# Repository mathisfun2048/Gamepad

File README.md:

# Gamepad

## Description and Exigence
Hallo! This is my second attempt at hardware design! This time, instead of focusing on a PCB, I wanted to investigate how multiple different parts can come together to create a product. The goal of this project is to create a functional gameboy-esq device that I can play games on! Initially this project was meant to fit inside of an altoids tin, but that was above my skill grade, so I downgraded to a slighly clunkier console. 

I have always enjoyed playing video games but never really considered how the hardware was created. So, this project hit 2 birds with 1 stone: I get a super cool gaming console to add to my collection and I get to learn about hardware >:) 
This project helped me get a glimse and greater appreciation of how hard hardware desgining and moreso planning. However, I picked up some cool skills which was really fun. 

A goal I had for this project specficially was to learn how to CAD using code, which I was able to do using a python script! I can't wait to see how it looks printed out irl. I have always been into coding and its been great seeing a way to directly merge my interest for talking with computers with creating something physical. 

Okay enough yap. If you want more stream of consciousness, look at my journal ;)

## PICTURES

### Schematic

### PCB 

### project as a whole

## Firmware
So tldr I don't know how to code games (yet!) so I will be utalizing RetroPi. It is not included in this repo because 1) github was being finicky about pushing it from my desktop folder and 2) its avalible online readilly 

## BOM

Here's everything you need if you want to build this too! (also includes sweat and tears... forgot to include that in the table)

Also, you might be wonderign why everything is either from Microcenter or Adafruit and not cheaper alternatives like AliExpress. The short answer is my parents won't allow me to purchase stuff from aliexpress. However, if my cost goes above the alloted $150 with future edits or anything, I will be more than happy to pay out of pocket. If this project gets downgraded to 4 points, I'd also be willing to pay out of pocket because this is honestly pretty cool and I want to see it in person. I never got a handheld video game console as a kid and I'm excited that I'll be able to make one now :)

| Item                      | Quantity | Cost          | Source      | Link                                                                                                                                          |
| ------------------------- | -------- | ------------- | ----------- | --------------------------------------------------------------------------------------------------------------------------------------------- |
| Raspberry Pi Zero 2       | 1        | 14.99         | Microcenter | [Link](https://www.microcenter.com/product/643085/raspberry-pi-zero-2-w)                                                                      |
| GPIO header               | 1        | 5.99          | Microcenter | [Link](https://www.microcenter.com/product/480889/schmartboard-inc-schmartboard-inc-2-x-20-male-headers-qty-5)                                |
| 2.2" Display              | 1        | 24.95         | Adafruit    | [Link](https://www.adafruit.com/product/2315)                                                                                                 |
| Custom PCB                | 1        | $9 + shipping | JCL PCB     |                                                                                                                                               |
| PowerBoost 1000c          | 1        | 19.99         | Microcenter | [Link](https://www.microcenter.com/product/474415/adafruit-industries-powerboost-1000-charger-rechargeable-5v-lipo-usb-boost-@-1a)            |
| 2500 mAh Battery          | 1        | 14.99         | Adafruit | [Link](https://www.microcenter.com/product/454401/adafruit-industries-lithium-ion-polymer-battery-37v-2500mah)                                |
| stacking header           | 1        | 2.95          | Adafruit    | [Link](https://www.adafruit.com/product/1979?srsltid=AfmBOoqbo1ndLmYMVLTt_bqD4Yhi48SgEFRf9jc0nGi86ePSABa_MOBi)                                |
| Slide Switch              | 1        | 0.95          | Adafruit    | [Link](https://www.adafruit.com/product/805)                                                                                                  |
| 6mm Tactile Buttons       | 10       | 9.99          | Microcenter | [Link](https://www.microcenter.com/product/632688/inland-6x6mm-micro-momentary-tactile-push-button-switches-assortment-kit-10-values-180-pcs) |
| #4-40 3/8" Machine Screws | 14       | 0.00          | Myself      | n/a                                                                                                                                           |
| #2-56 3/8" Machine Screws | 6        | 0.00          | Myself      | n/a                                                                                                                                           |
| **Total**                 |  | **~110**      |             |

## Closing Remarks On Planning

This has been such a fun thing to fall into this rabbithole where I could desing this. Without Highway (shoutout Hack Club!) I would never have learned this much about hardware in such a short time; I am very grateful for this opportunity. While I do have to part now, I can't wait to build it and enter in my final remarks after I get this to work!

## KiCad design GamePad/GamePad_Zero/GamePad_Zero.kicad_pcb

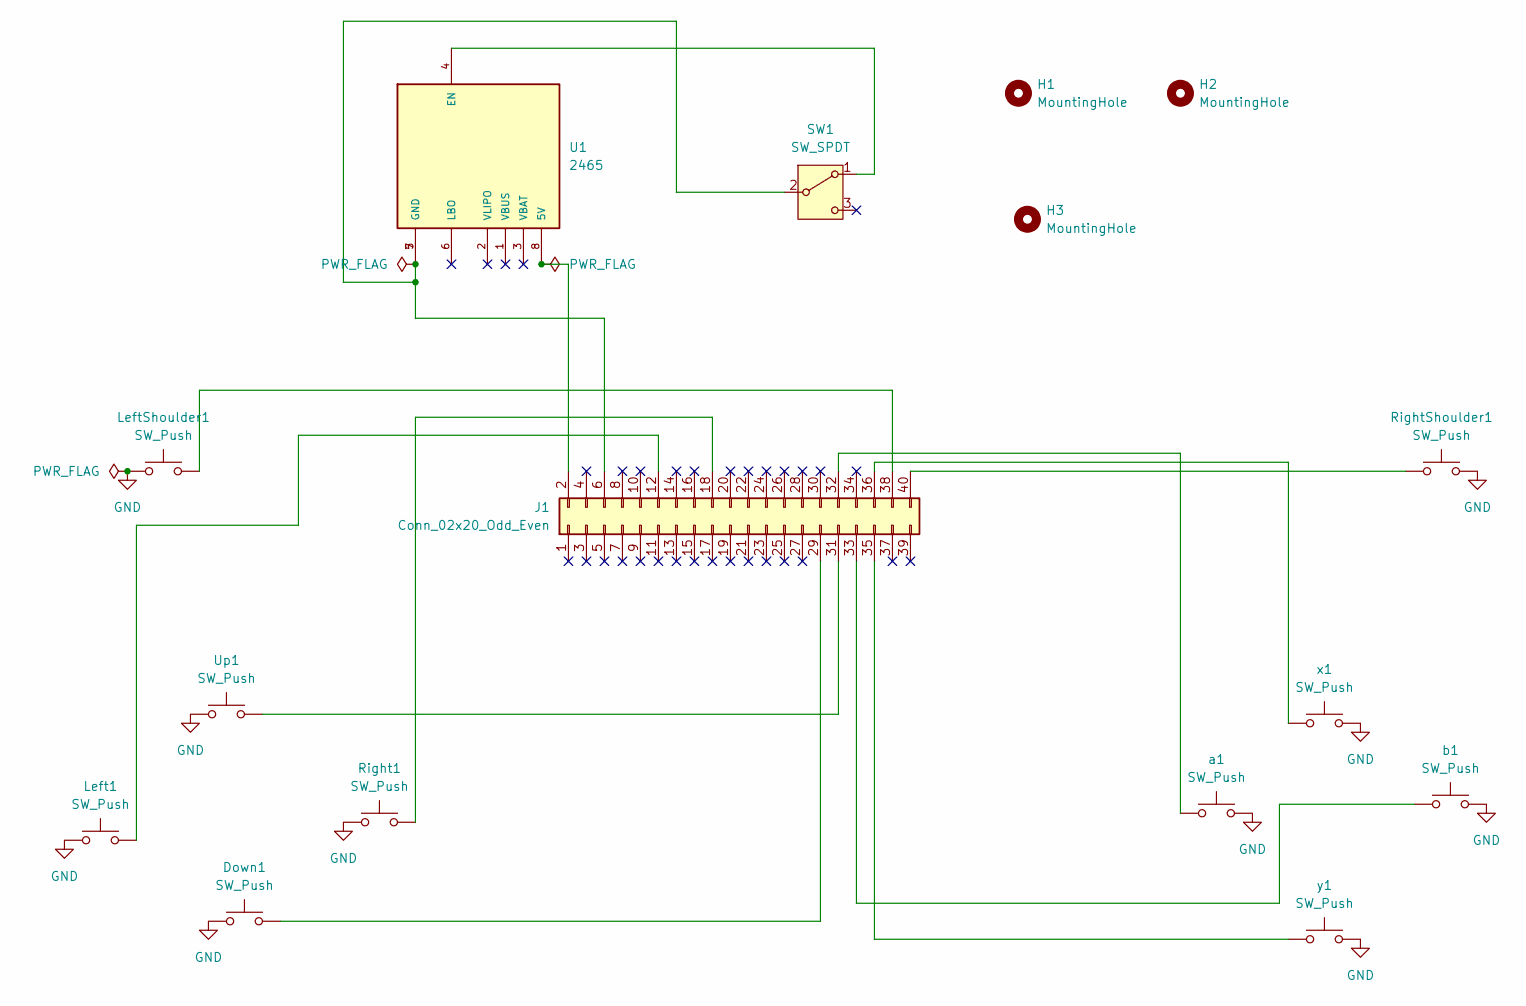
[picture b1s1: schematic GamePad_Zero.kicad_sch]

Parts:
Down1: SW_Push; SW_PUSH_6mm
H1, H2, H3: MountingHole; MountingHole_2.5mm
J1: Conn_02x20_Odd_Even; MODULE_SC1176
Left1: SW_Push; SW_PUSH_6mm
LeftShoulder1: SW_Push; SW_PUSH_6mm
Right1: SW_Push; SW_PUSH_6mm
RightShoulder1: SW_Push; SW_PUSH_6mm
SW1: SW_SPDT; SW_MINI-SPDT-SW
U1: 2465; MODULE_2465; PARTREV B
Up1: SW_Push; SW_PUSH_6mm
a1: SW_Push; SW_PUSH_6mm
b1: SW_Push; SW_PUSH_6mm
x1: SW_Push; SW_PUSH_6mm
y1: SW_Push; SW_PUSH_6mm

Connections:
GND: Down1.1, Left1.1, LeftShoulder1.1, Right1.1, RightShoulder1.2, Up1.1, a1.2, b1.2, x1.2, y1.2
unnamed: J1.2, U1.8 (5V)
unnamed: J1.6, SW1.2 (B), U1.5 (GND), U1.7 (GND)
unnamed: J1.12, Left1.2
unnamed: J1.18, Right1.2
unnamed: Down1.2, J1.29
unnamed: J1.31, Up1.2
unnamed: J1.32, a1.1
unnamed: J1.33, b1.1
unnamed: J1.35, y1.1
unnamed: J1.36, x1.1
unnamed: J1.38, LeftShoulder1.2
unnamed: J1.40, RightShoulder1.1
unnamed: SW1.1 (A), U1.4 (EN)

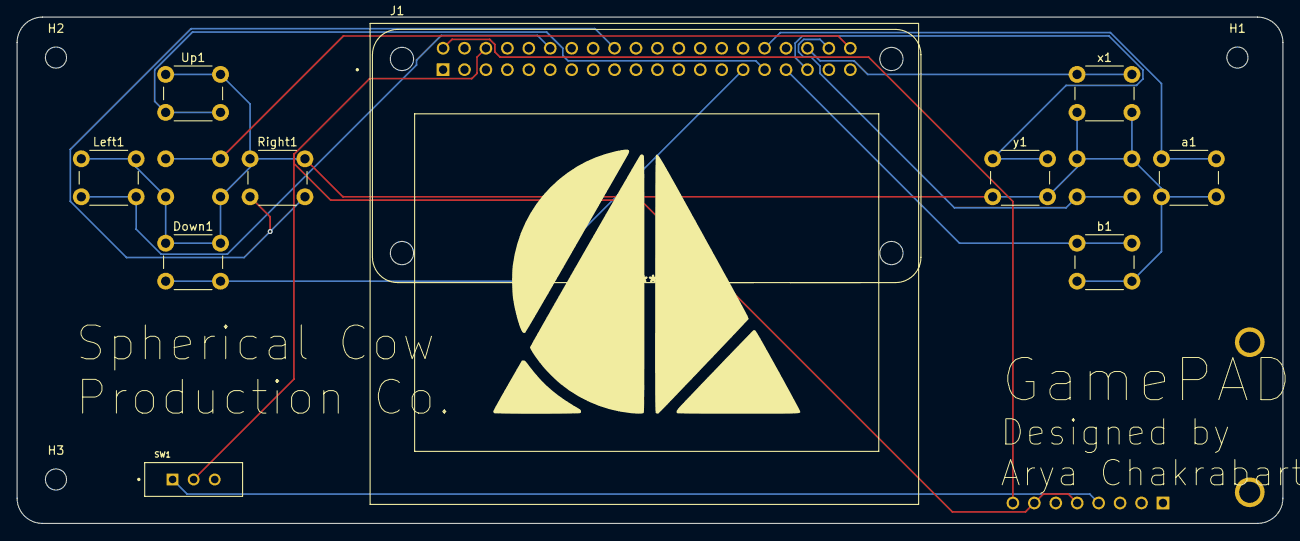
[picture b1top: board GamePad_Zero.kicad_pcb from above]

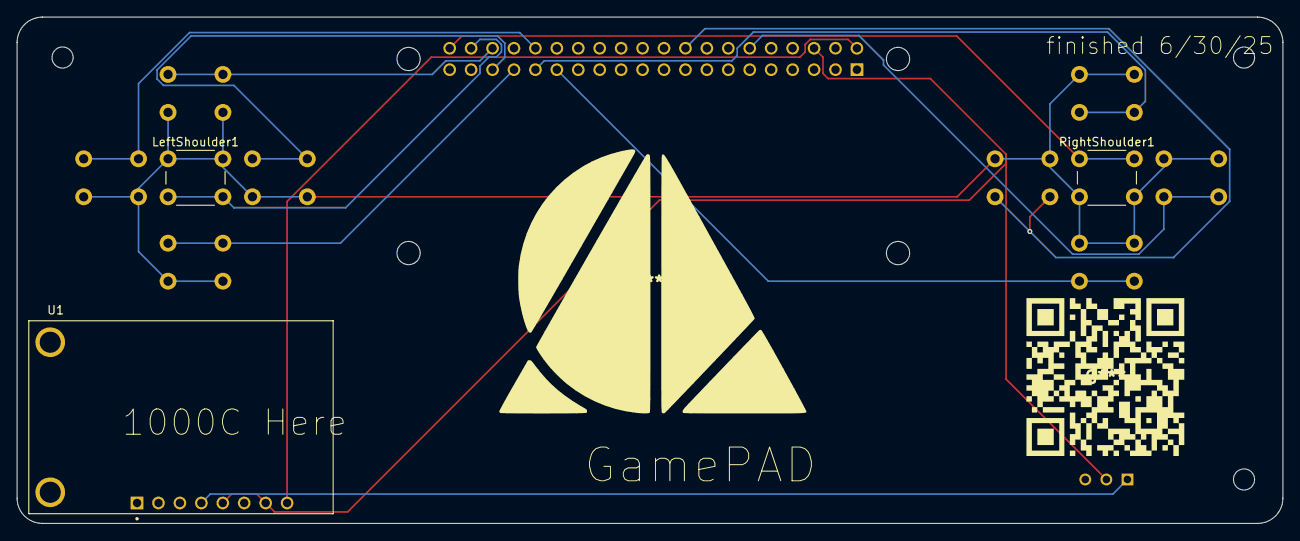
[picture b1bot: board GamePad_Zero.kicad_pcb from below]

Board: 2 copper layers, 150.0 x 60.0 mm, 16 parts (3 on the bottom side), 14 nets.

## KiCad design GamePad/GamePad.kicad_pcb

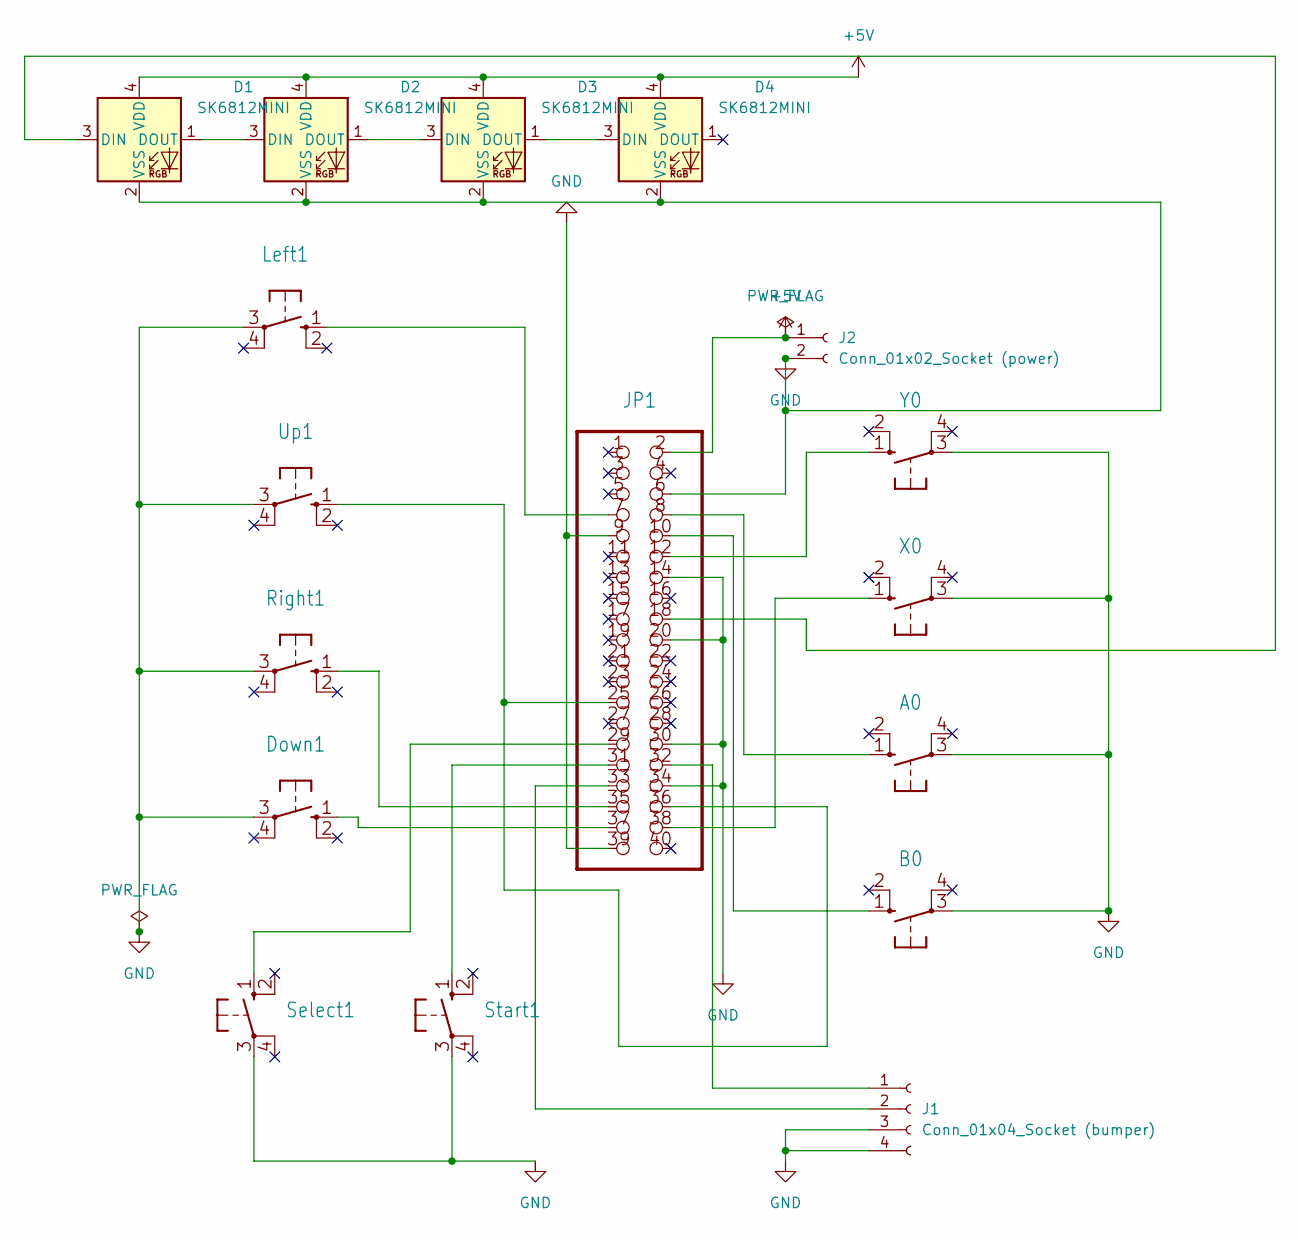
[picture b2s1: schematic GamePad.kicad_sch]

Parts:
A0: B3F-10XX
B0: B3F-10XX
D1, D2, D3, D4: SK6812MINI; LED_SK6812MINI_PLCC4_3.5x3.5mm_P1.75mm
Down1: B3F-10XX
J1: Conn_01x04_Socket (bumper); 1X04
J2: Conn_01x02_Socket (power); 1X02
JP1: 2X20
Left1: B3F-10XX
Right1: B3F-10XX
Select1: B3F-10XX
Start1: B3F-10XX
Up1: B3F-10XX
X0: B3F-10XX
Y0: B3F-10XX

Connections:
+5V: D1.4 (VDD), D2.4 (VDD), D3.4 (VDD), D4.4 (VDD), J2.1, JP1.2
GND: A0.3, B0.3, D1.2 (VSS), D2.2 (VSS), D3.2 (VSS), D4.2 (VSS), Down1.3, J1.3, J1.4, J2.2, JP1.6, JP1.9, JP1.14, JP1.20, JP1.30, JP1.34, JP1.39, Left1.3, Right1.3, Select1.3, Start1.3, Up1.3, X0.3, Y0.3
unnamed: A0.1 (S), JP1.8
unnamed: B0.1 (S), JP1.10
unnamed: D1.3 (DIN), JP1.18
unnamed: D1.1 (DOUT), D2.3 (DIN)
unnamed: D2.1 (DOUT), D3.3 (DIN)
unnamed: D3.1 (DOUT), D4.3 (DIN)
unnamed: Down1.1 (S), JP1.37
unnamed: J1.1, JP1.32
unnamed: J1.2, JP1.33
unnamed: JP1.7, Left1.1 (S)
unnamed: JP1.35, Right1.1 (S)
unnamed: JP1.29, Select1.1 (S)
unnamed: JP1.31, Start1.1 (S)
unnamed: JP1.25, JP1.36, Up1.1 (S)
unnamed: JP1.38, X0.1 (S)
unnamed: JP1.12, Y0.1 (S)

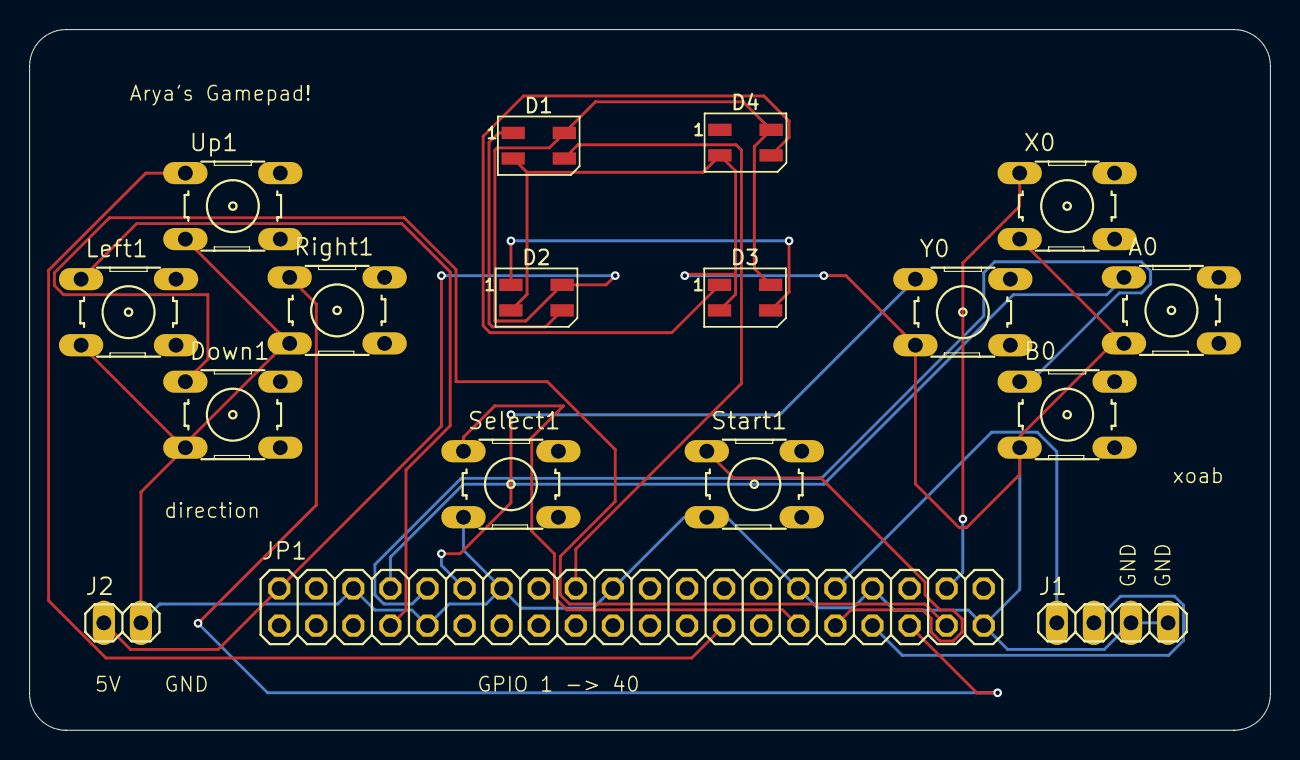
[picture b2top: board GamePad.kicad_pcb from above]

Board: 2 copper layers, 85.0 x 48.0 mm, 17 parts (0 on the bottom side), 18 nets.

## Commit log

2025-06-19 Initial clean commit
2025-06-20 new cad files!
2025-06-20 deleted old cad files
2025-06-20 added STEP files
2025-06-22 some misc. files added
2025-06-22 added some misc files
2025-06-23 added custom PCB
2025-06-30 finished new PCB
2025-07-01 finishing touches
